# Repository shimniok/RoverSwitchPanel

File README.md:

# RoverSwitchPanel
Switch panel for autonomous rover (or whatever else)

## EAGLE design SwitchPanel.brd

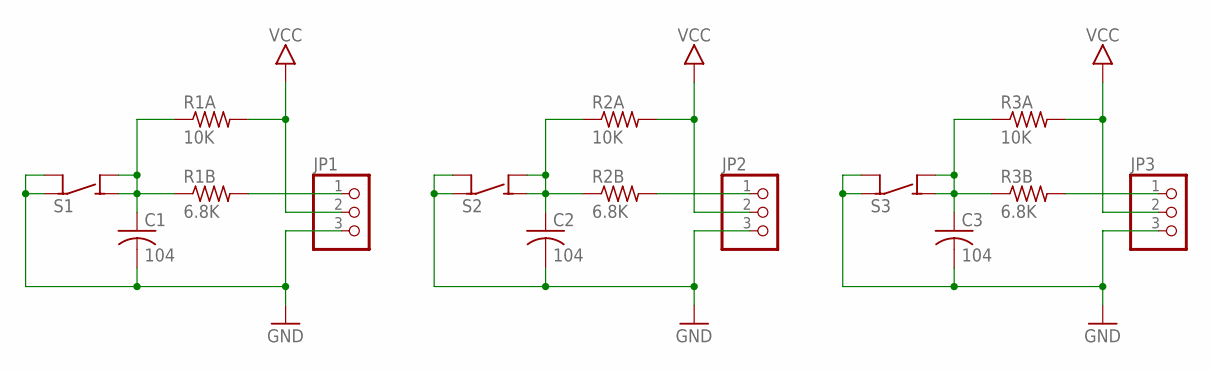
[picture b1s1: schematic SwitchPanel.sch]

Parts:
C1, C2, C3: 104; C075
JP1, JP2, JP3: PINHD-1X03_2.54-90°-S; 1X03/90-S
R1A, R2A, R3A: 10K; 0207/7
R1B, R2B, R3B: 6.8K; 0207/7
S1, S2, S3: SPST412MM; 12MMTACTILE_4PIN

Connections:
GND: C1.2 (-), C2.2 (-), C3.2 (-), JP1.3, JP2.3, JP3.3, S1.P1A (COM), S1.P1B (COM), S2.P1A (COM), S2.P1B (COM), S3.P1A (COM), S3.P1B (COM)
unnamed: C2.1 (+), R2A.1, R2B.1, S2.P2A (NO), S2.P2B (NO)
unnamed: C1.1 (+), R1A.1, R1B.1, S1.P2A (NO), S1.P2B (NO)
unnamed: JP1.1, R1B.2
unnamed: JP2.1, R2B.2
unnamed: C3.1 (+), R3A.1, R3B.1, S3.P2A (NO), S3.P2B (NO)
unnamed: JP3.1, R3B.2
VCC: JP1.2, JP2.2, JP3.2, R1A.2, R2A.2, R3A.2

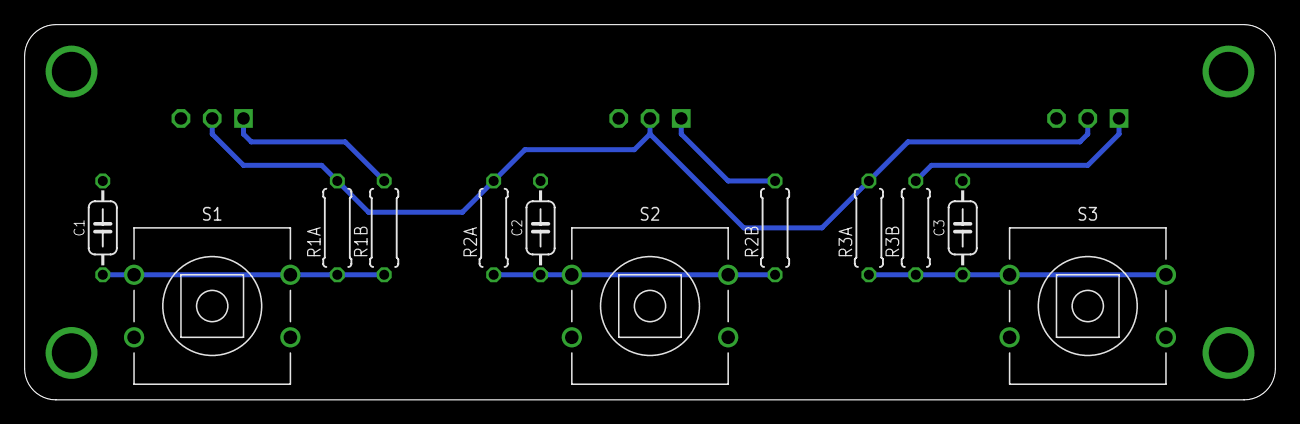
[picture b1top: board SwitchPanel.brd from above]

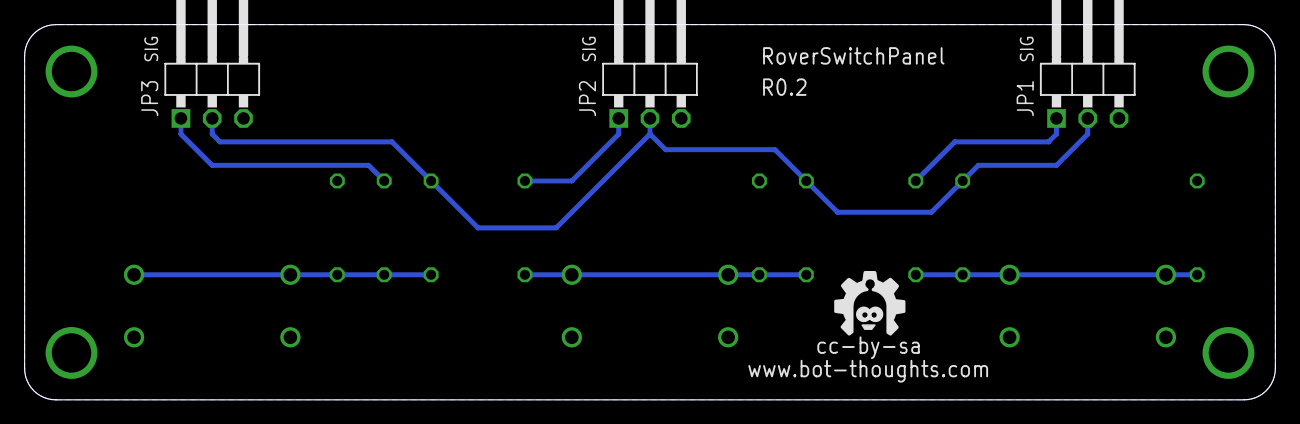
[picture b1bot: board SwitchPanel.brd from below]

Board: 2 copper layers, 101.6 x 30.5 mm, 16 parts (4 on the bottom side), 8 nets.

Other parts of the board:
U$4: BTLOGOM

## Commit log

2019-01-01 initial
2019-01-01 Moved logo to bottom silk
2019-01-02 corrected signal pin silkscreen

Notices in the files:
SwitchPanel.brd:
cc-by-sa
